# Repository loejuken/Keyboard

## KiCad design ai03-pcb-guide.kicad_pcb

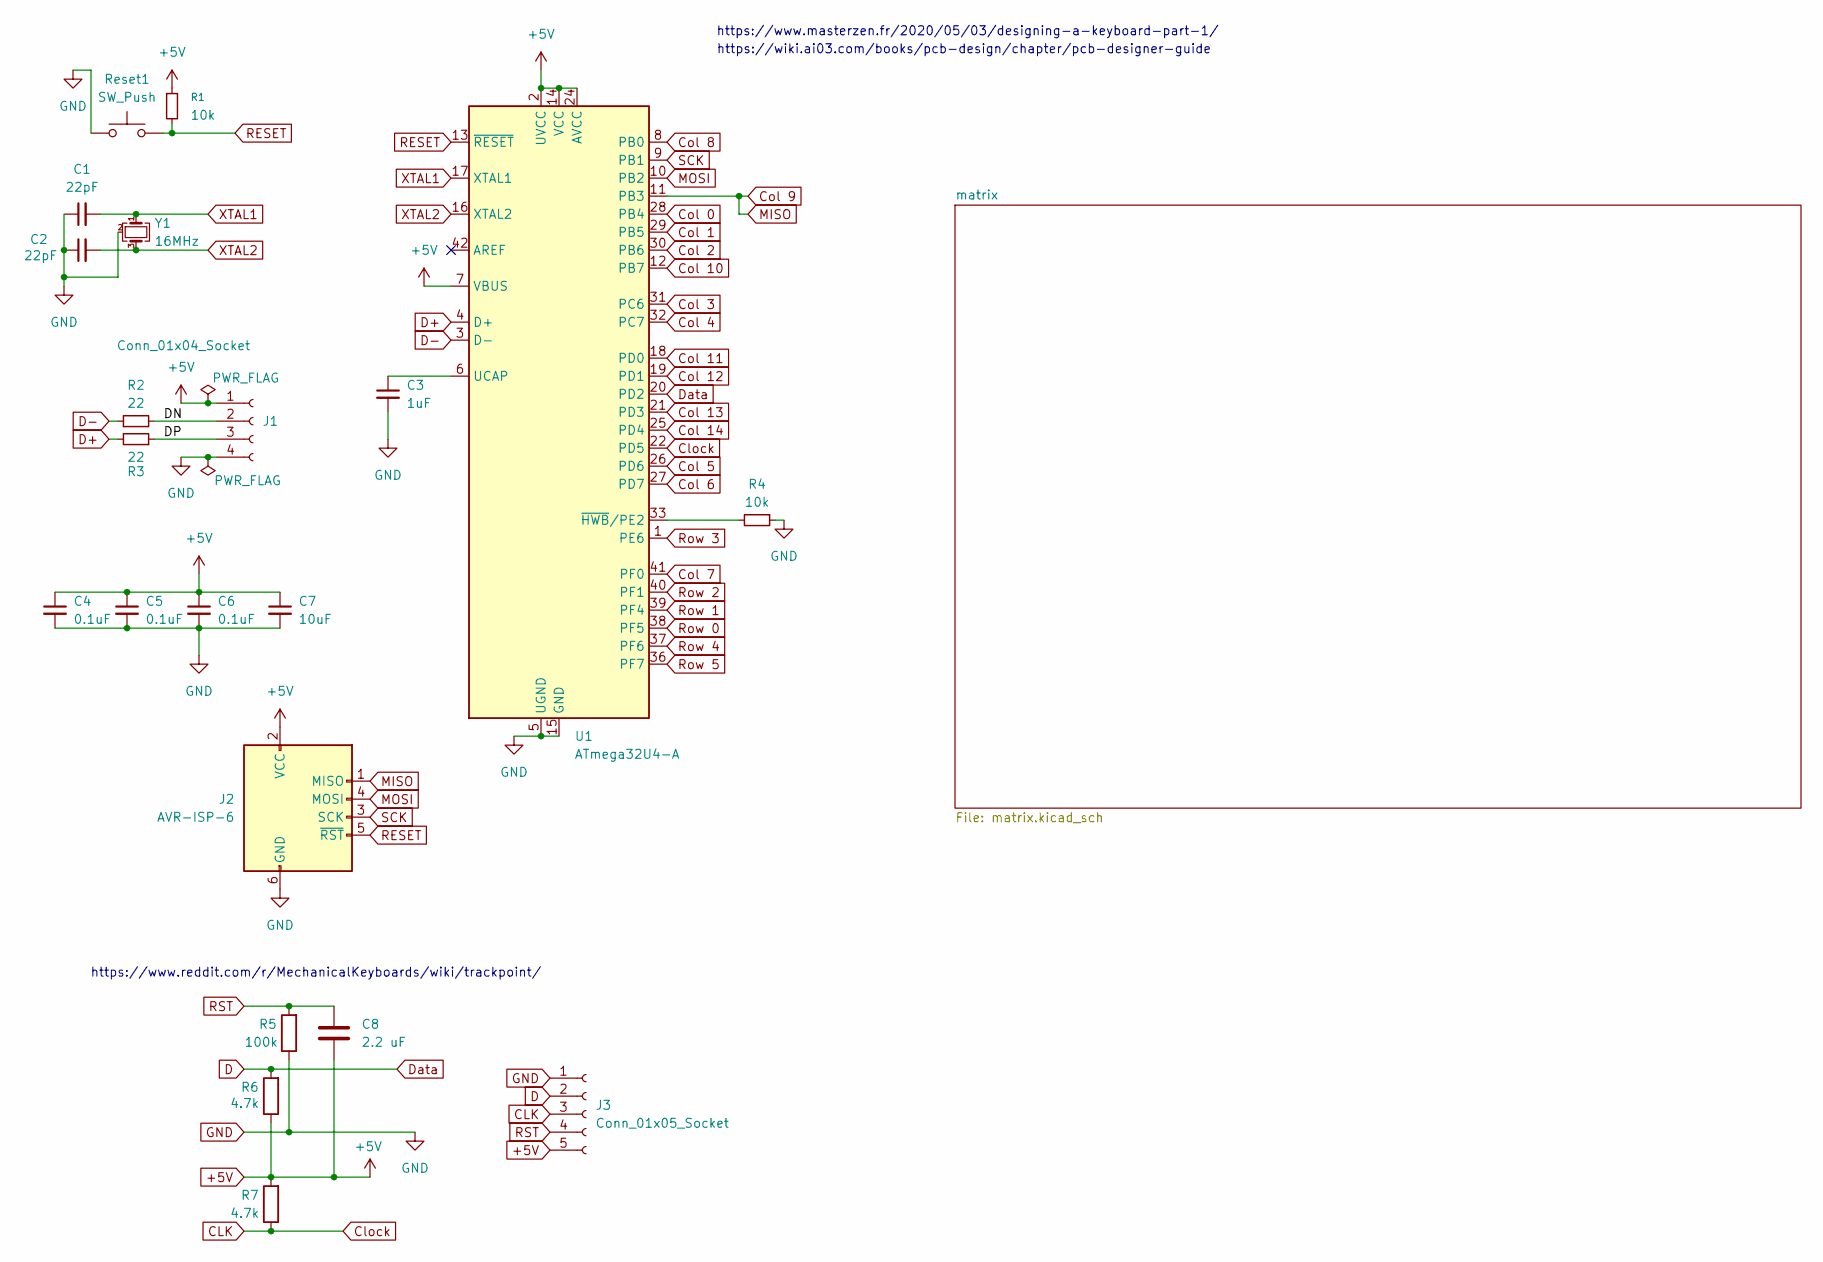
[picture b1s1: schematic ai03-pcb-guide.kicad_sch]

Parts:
C1, C2: 22pF; C_0603_1608Metric
C3: 1uF; C_0603_1608Metric
C4, C5, C6: 0.1uF; C_0603_1608Metric
C7: 10uF; C_0603_1608Metric
C8: 2.2 uF; C_0603_1608Metric
J1: Conn_01x04_Socket; Molex_Pico-EZmate_78171-0004_1x04-1MP_P1.20mm_Vertical
J2: AVR-ISP-6; Reset_Pretty-Mask
J3: Conn_01x05_Socket; Molex_Pico-EZmate_78171-0005_1x05-1MP_P1.20mm_Vertical
R1, R4: 10k; R_0603_1608Metric
R2, R3: 22; R_0603_1608Metric
R5: 100k; R_0603_1608Metric
R6, R7: 4.7k; R_0603_1608Metric
Reset1: SW_Push; SW_SPST_SKQG_WithStem
U1: ATmega32U4-A; TQFP-44_10x10mm_P0.8mm
Y1: 16MHz; Crystal_SMD_3225-4Pin_3.2x2.5mm

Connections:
+5V: C4.1, C5.1, C6.1, C7.1, C8.2, J1.1, J2.2 (VCC), J3.5, R1.1, R6.1, R7.2, U1.2 (UVCC), U1.7 (VBUS), U1.14 (VCC), U1.24 (AVCC), U1.34 (VCC), U1.44 (AVCC)
/DN: J1.2, R2.2
/DP: J1.3, R3.1
CLK: J3.3, R7.1, U1.22 (PD5)
Col 0: U1.28 (PB4); also elsewhere on the board
Col 1: U1.29 (PB5); also elsewhere on the board
Col 2: U1.30 (PB6); also elsewhere on the board
Col 3: U1.31 (PC6); also elsewhere on the board
Col 4: U1.32 (PC7); also elsewhere on the board
Col 5: U1.26 (PD6); also elsewhere on the board
Col 6: U1.27 (PD7); also elsewhere on the board
Col 7: U1.41 (PF0); also elsewhere on the board
Col 8: U1.8 (PB0); also elsewhere on the board
Col 9: J2.1 (MISO), U1.11 (PB3); also elsewhere on the board
Col 10: U1.12 (PB7); also elsewhere on the board
Col 11: U1.18 (PD0); also elsewhere on the board
Col 12: U1.19 (PD1); also elsewhere on the board
Col 13: U1.21 (PD3); also elsewhere on the board
Col 14: U1.25 (PD4); also elsewhere on the board
D: J3.2, R6.2, U1.20 (PD2)
D+: R3.2, U1.4 (D+)
D-: R2.1, U1.3 (D-)
GND: C1.1, C2.1, C3.2, C4.2, C5.2, C6.2, C7.2, J1.4, J2.6 (GND), J3.1, R4.1, R5.1, Reset1.1, U1.5 (UGND), U1.15 (GND), U1.23 (GND), U1.35 (GND), U1.43 (GND), Y1.2 (G), Y1.4 (G)
MOSI: J2.4 (MOSI), U1.10 (PB2)
unnamed: C3.1, U1.6 (UCAP)
unnamed: R4.2, U1.33 (~HWB/PE2)
RESET: J2.5 (~RST), R1.2, Reset1.2, U1.13 (~RESET)
RST: C8.1, J3.4, R5.2
Row 0: U1.38 (PF5); also elsewhere on the board
Row 1: U1.39 (PF4); also elsewhere on the board
Row 2: U1.40 (PF1); also elsewhere on the board
Row 3: U1.1 (PE6); also elsewhere on the board
Row 4: U1.37 (PF6); also elsewhere on the board
Row 5: U1.36 (PF7); also elsewhere on the board
SCK: J2.3 (SCK), U1.9 (PB1)
XTAL1: C1.2, U1.17 (XTAL1), Y1.1
XTAL2: C2.2, U1.16 (XTAL2), Y1.3

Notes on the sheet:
https://www.masterzen.fr/2020/05/03/designing-a-keyboard-part-1/
https://wiki.ai03.com/books/pcb-design/chapter/pcb-designer-guide
https://www.reddit.com/r/MechanicalKeyboards/wiki/trackpoint/

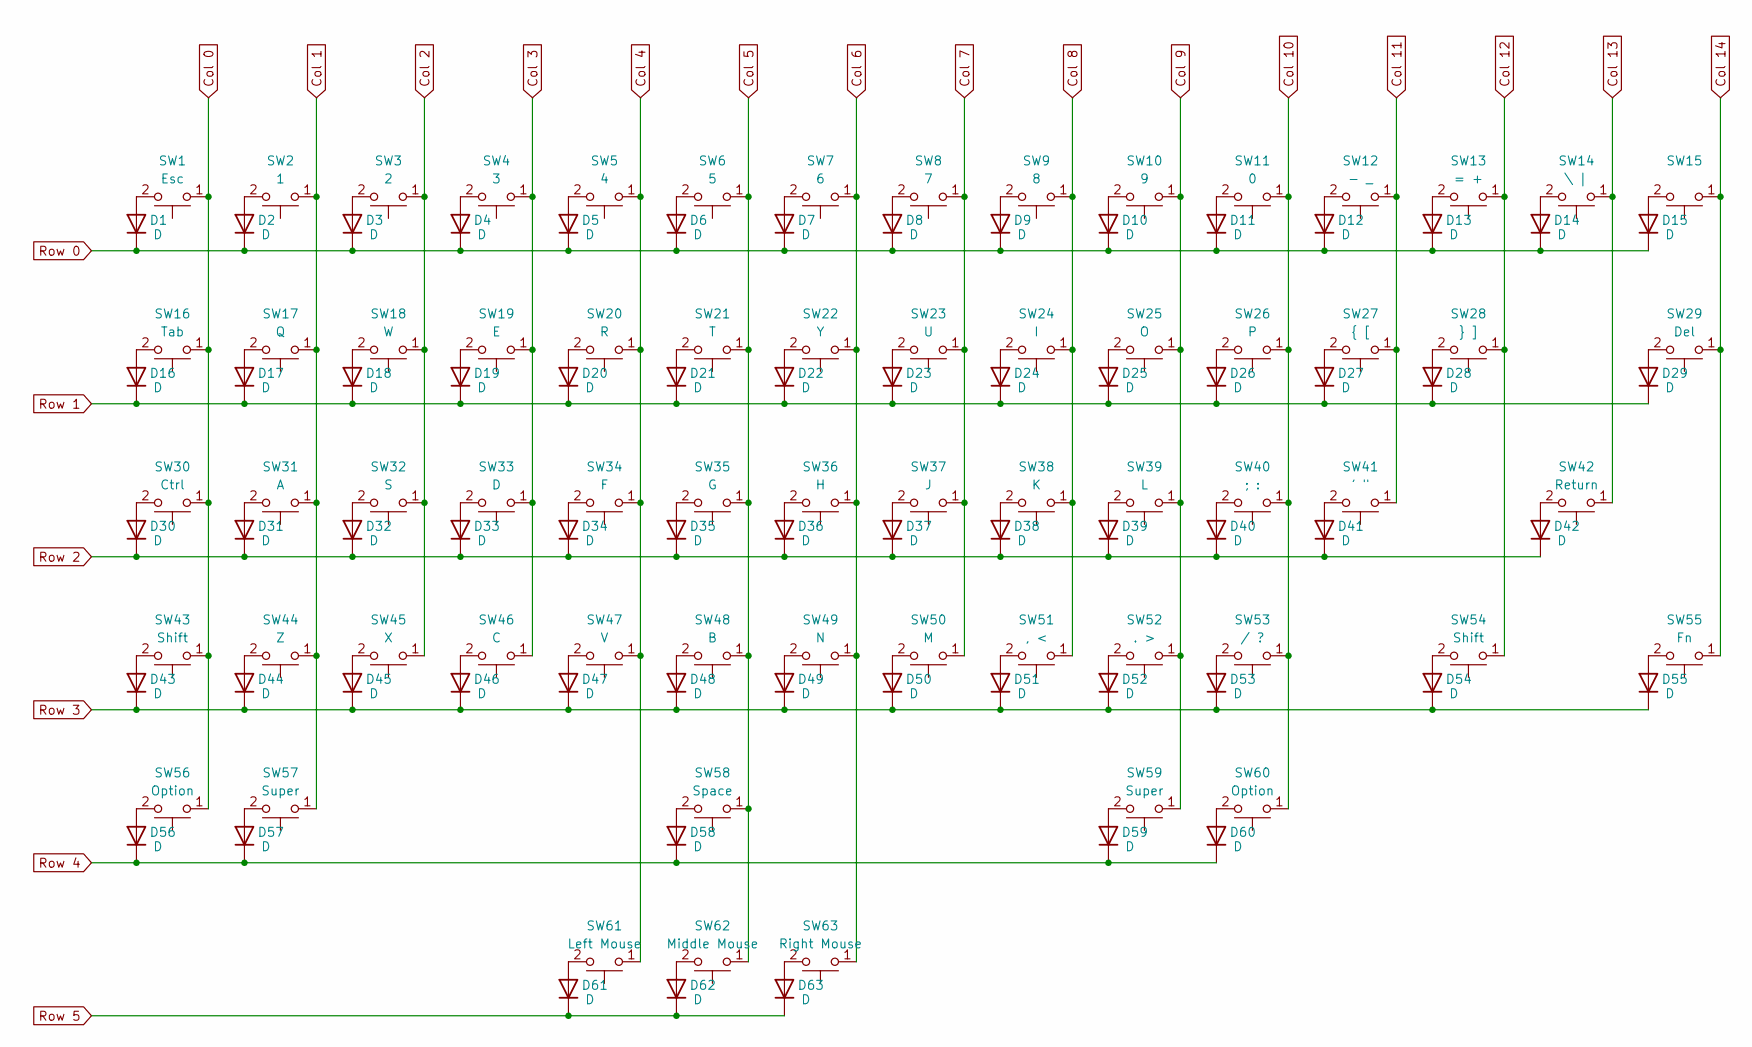
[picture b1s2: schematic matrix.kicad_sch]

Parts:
D1, D2, D3, D4, D5, D6, D7, D8, D9, D10, D11, D12, D13, D14, D15, D16, D17, D18, D19, D20, D21, D22, D23, D24, D25, D26, D27, D28, D29, D30, D31, D32, D33, D34, D35, D36, D37, D38, D39, D40, D41, D42, D43, D44, D45, D46, D47, D48, D49, D50, D51, D52, D53, D54, D55, D56, D57, D58, D59, D60, D61, D62, D63: D; D_SOD-123; LCSC Part # C83528
SW1: Esc; MXOnly-1U
SW2: 1; MXOnly-1U
SW3: 2; MXOnly-1U
SW4: 3; MXOnly-1U
SW5: 4; MXOnly-1U
SW6: 5; MXOnly-1U
SW7: 6; MXOnly-1U
SW8: 7; MXOnly-1U
SW9: 8; MXOnly-1U
SW10: 9; MXOnly-1U
SW11: 0; MXOnly-1U
SW12: - _; MXOnly-1U
SW13: = +; MXOnly-1U
SW14: \ |; MXOnly-1U
SW15: MXOnly-1U
SW16: Tab; MXOnly-1.5U
SW17: Q; MXOnly-1U
SW18: W; MXOnly-1U
SW19: E; MXOnly-1U
SW20: R; MXOnly-1U
SW21: T; MXOnly-1U
SW22: Y; MXOnly-1U
SW23: U; MXOnly-1U
SW24: I; MXOnly-1U
SW25: O; MXOnly-1U
SW26: P; MXOnly-1U
SW27: { [; MXOnly-1U
SW28: } ]; MXOnly-1U
SW29: Del; MXOnly-1.5U
SW30: Ctrl; MXOnly-1.75U
SW31: A; MXOnly-1U
SW32: S; MXOnly-1U
SW33: D; MXOnly-1U
SW34: F; MXOnly-1U
SW35: G; MXOnly-1U
SW36: H; MXOnly-1U
SW37: J; MXOnly-1U
SW38: K; MXOnly-1U
SW39: L; MXOnly-1U
SW40: ; :; MXOnly-1U
SW41: ' "; MXOnly-1U
SW42: Return; MXOnly-2.25U
SW43: Shift; MXOnly-2.25U-ReversedStabilizers-NoLED
SW44: Z; MXOnly-1U
SW45: X; MXOnly-1U
SW46: C; MXOnly-1U
SW47: V; MXOnly-1U
SW48: B; MXOnly-1U
SW49: N; MXOnly-1U
SW50: M; MXOnly-1U
SW51: , <; MXOnly-1U
SW52: . >; MXOnly-1U
SW53: / ?; MXOnly-1U
SW54: Shift; MXOnly-1.75U
SW55: Fn; MXOnly-1U
SW56, SW60: Option; MXOnly-1U
SW57, SW59: Super; MXOnly-1.5U
SW58: Space; MXOnly-6U-ReversedStabilizers-NoLED
SW61: Left Mouse; KailhChoc-1.5U
SW62: Middle Mouse; KailhChoc-1U
SW63: Right Mouse; KailhChoc-1.5U

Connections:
Col 0: SW1.1, SW16.1, SW30.1, SW43.1, SW56.1; also elsewhere on the board
Col 1: SW2.1, SW17.1, SW31.1, SW44.1, SW57.1; also elsewhere on the board
Col 2: SW3.1, SW18.1, SW32.1, SW45.1; also elsewhere on the board
Col 3: SW4.1, SW19.1, SW33.1, SW46.1; also elsewhere on the board
Col 4: SW5.1, SW20.1, SW34.1, SW47.1, SW61.1; also elsewhere on the board
Col 5: SW6.1, SW21.1, SW35.1, SW48.1, SW58.1, SW62.1; also elsewhere on the board
Col 6: SW7.1, SW22.1, SW36.1, SW49.1, SW63.1; also elsewhere on the board
Col 7: SW8.1, SW23.1, SW37.1, SW50.1; also elsewhere on the board
Col 8: SW9.1, SW24.1, SW38.1, SW51.1; also elsewhere on the board
Col 9: SW10.1, SW25.1, SW39.1, SW52.1, SW59.1; also elsewhere on the board
Col 10: SW11.1, SW26.1, SW40.1, SW53.1, SW60.1; also elsewhere on the board
Col 11: SW12.1, SW27.1, SW41.1; also elsewhere on the board
Col 12: SW13.1, SW28.1, SW54.1; also elsewhere on the board
Col 13: SW14.1, SW42.1; also elsewhere on the board
Col 14: SW15.1, SW29.1, SW55.1; also elsewhere on the board
unnamed: D1.2 (A), SW1.2
unnamed: D2.2 (A), SW2.2
unnamed: D3.2 (A), SW3.2
unnamed: D4.2 (A), SW4.2
unnamed: D5.2 (A), SW5.2
unnamed: D6.2 (A), SW6.2
unnamed: D7.2 (A), SW7.2
unnamed: D8.2 (A), SW8.2
unnamed: D9.2 (A), SW9.2
unnamed: D10.2 (A), SW10.2
unnamed: D11.2 (A), SW11.2
unnamed: D12.2 (A), SW12.2
unnamed: D13.2 (A), SW13.2
unnamed: D14.2 (A), SW14.2
unnamed: D15.2 (A), SW15.2
unnamed: D16.2 (A), SW16.2
unnamed: D17.2 (A), SW17.2
unnamed: D18.2 (A), SW18.2
unnamed: D19.2 (A), SW19.2
unnamed: D20.2 (A), SW20.2
unnamed: D21.2 (A), SW21.2
unnamed: D22.2 (A), SW22.2
unnamed: D23.2 (A), SW23.2
unnamed: D24.2 (A), SW24.2
unnamed: D25.2 (A), SW25.2
unnamed: D26.2 (A), SW26.2
unnamed: D27.2 (A), SW27.2
unnamed: D28.2 (A), SW28.2
unnamed: D29.2 (A), SW29.2
unnamed: D30.2 (A), SW30.2
unnamed: D31.2 (A), SW31.2
unnamed: D32.2 (A), SW32.2
unnamed: D33.2 (A), SW33.2
unnamed: D34.2 (A), SW34.2
unnamed: D35.2 (A), SW35.2
unnamed: D36.2 (A), SW36.2
unnamed: D37.2 (A), SW37.2
unnamed: D38.2 (A), SW38.2
unnamed: D39.2 (A), SW39.2
unnamed: D40.2 (A), SW40.2
unnamed: D41.2 (A), SW41.2
unnamed: D42.2 (A), SW42.2
unnamed: D43.2 (A), SW43.2
unnamed: D44.2 (A), SW44.2
unnamed: D45.2 (A), SW45.2
unnamed: D46.2 (A), SW46.2
unnamed: D47.2 (A), SW47.2
unnamed: D48.2 (A), SW48.2
unnamed: D49.2 (A), SW49.2
unnamed: D50.2 (A), SW50.2
unnamed: D51.2 (A), SW51.2
unnamed: D52.2 (A), SW52.2
unnamed: D53.2 (A), SW53.2
unnamed: D54.2 (A), SW54.2
unnamed: D55.2 (A), SW55.2
unnamed: D56.2 (A), SW56.2
unnamed: D57.2 (A), SW57.2
unnamed: D58.2 (A), SW58.2
unnamed: D59.2 (A), SW59.2
unnamed: D60.2 (A), SW60.2
unnamed: D61.2 (A), SW61.2
unnamed: D62.2 (A), SW62.2
unnamed: D63.2 (A), SW63.2
Row 0: D1.1 (K), D2.1 (K), D3.1 (K), D4.1 (K), D5.1 (K), D6.1 (K), D7.1 (K), D8.1 (K), D9.1 (K), D10.1 (K), D11.1 (K), D12.1 (K), D13.1 (K), D14.1 (K), D15.1 (K); also elsewhere on the board
Row 1: D16.1 (K), D17.1 (K), D18.1 (K), D19.1 (K), D20.1 (K), D21.1 (K), D22.1 (K), D23.1 (K), D24.1 (K), D25.1 (K), D26.1 (K), D27.1 (K), D28.1 (K), D29.1 (K); also elsewhere on the board
Row 2: D30.1 (K), D31.1 (K), D32.1 (K), D33.1 (K), D34.1 (K), D35.1 (K), D36.1 (K), D37.1 (K), D38.1 (K), D39.1 (K), D40.1 (K), D41.1 (K), D42.1 (K); also elsewhere on the board
Row 3: D43.1 (K), D44.1 (K), D45.1 (K), D46.1 (K), D47.1 (K), D48.1 (K), D49.1 (K), D50.1 (K), D51.1 (K), D52.1 (K), D53.1 (K), D54.1 (K), D55.1 (K); also elsewhere on the board
Row 4: D56.1 (K), D57.1 (K), D58.1 (K), D59.1 (K), D60.1 (K); also elsewhere on the board
Row 5: D61.1 (K), D62.1 (K), D63.1 (K); also elsewhere on the board

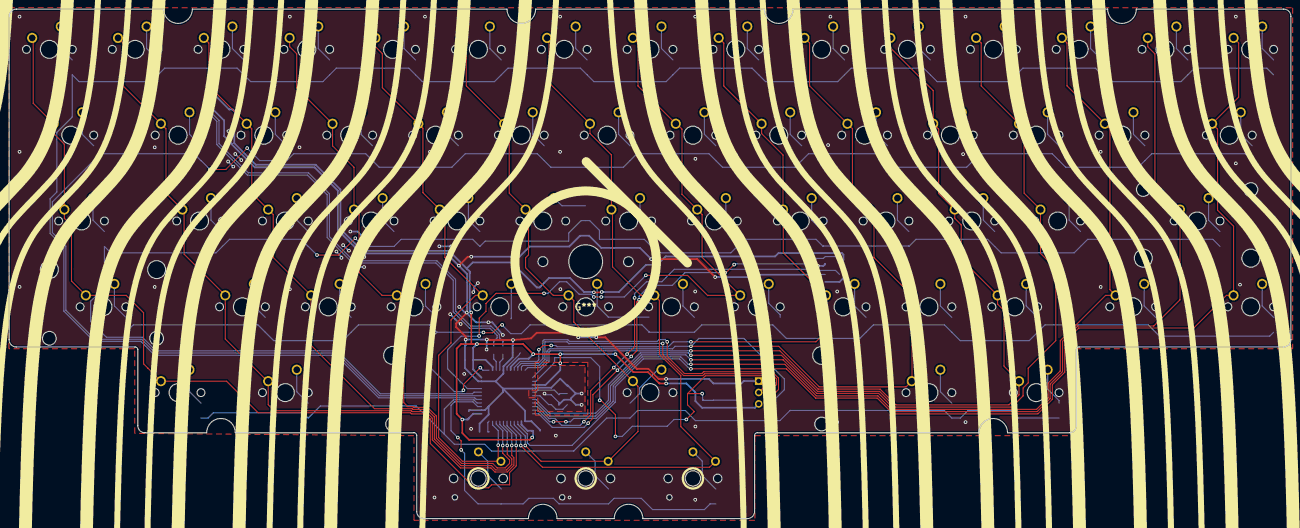
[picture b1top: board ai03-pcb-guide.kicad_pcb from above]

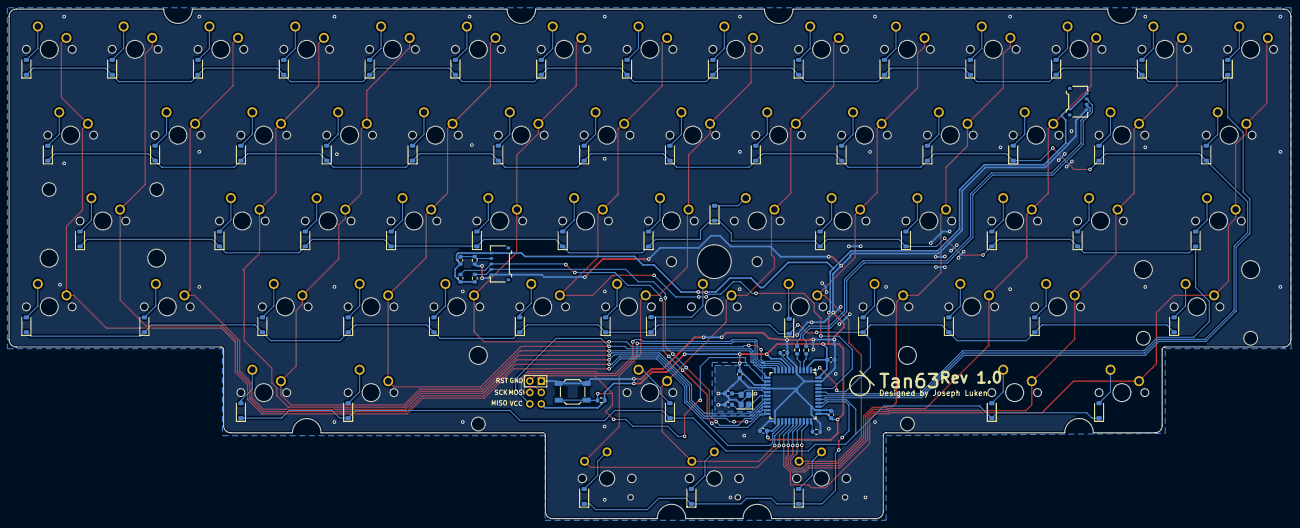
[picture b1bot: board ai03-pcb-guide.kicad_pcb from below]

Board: 2 copper layers, 284.5 x 113.1 mm, 147 parts (84 on the bottom side), 100 nets.

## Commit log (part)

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2026-06-08 Project file setup
2026-06-08 Add submodules
2026-06-08 Added libraries
2026-06-08 New Type C Lib and early MCU Schema
2026-06-09 more MCU schema
2026-06-10 MCU schema and matrix schema
2026-06-12 schema mostly done with footprints added
2026-06-12 schema and pcb changes
2026-06-14 pcb finished except for routing
2026-06-14 more revisions
2026-06-15 fixing issues
2026-06-21 changed footprints because I did them wrong
